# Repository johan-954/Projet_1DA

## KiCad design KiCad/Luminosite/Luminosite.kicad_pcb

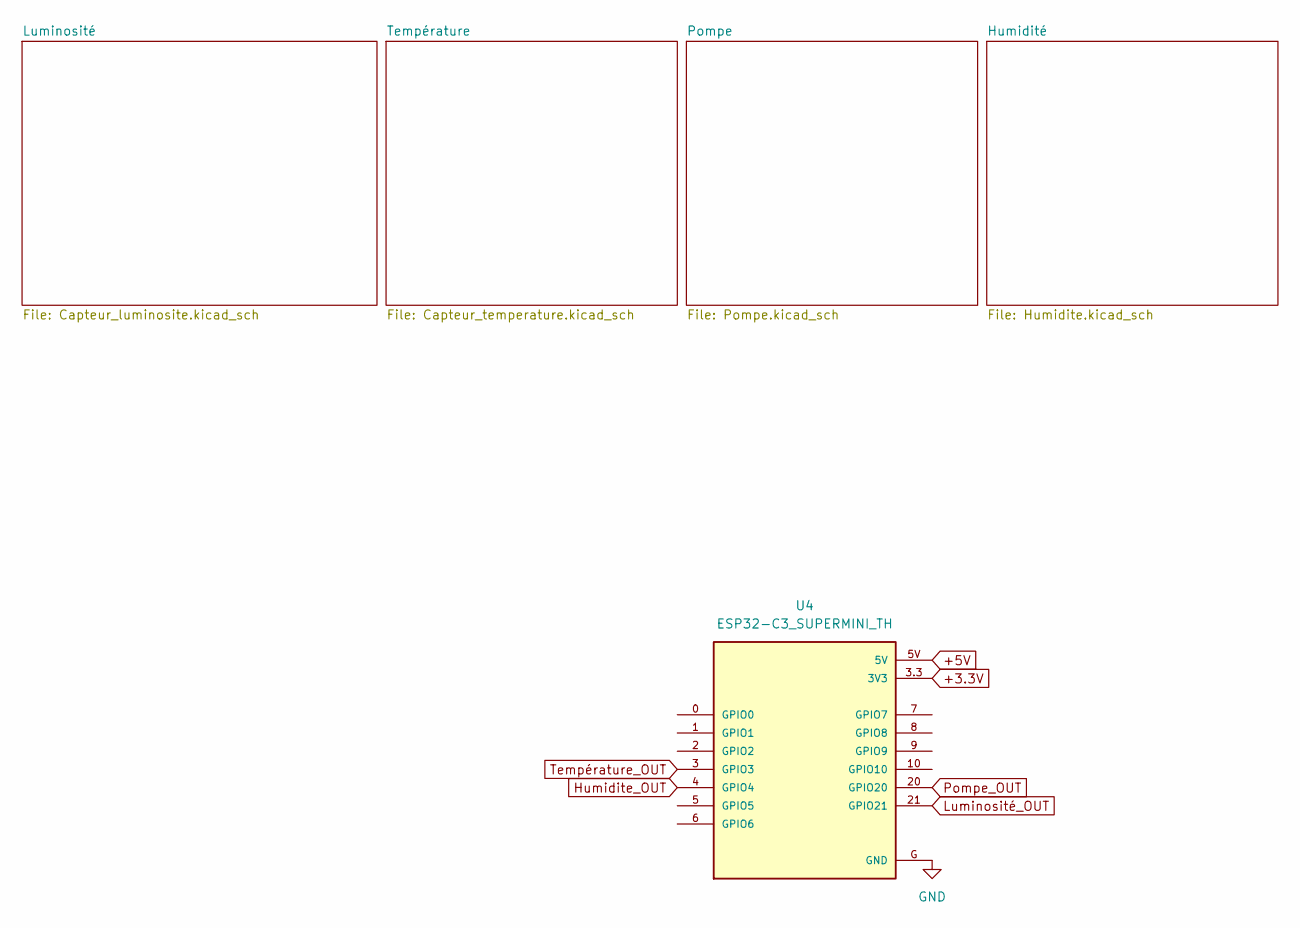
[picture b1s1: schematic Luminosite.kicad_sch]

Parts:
U4: ESP32-C3_SUPERMINI_TH; MODULE_ESP32-C3_SUPERMINI_TH

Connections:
+3.3V: U4.3.3 (3V3); also elsewhere on the board
+5V: U4.5V; also elsewhere on the board
GND: U4.G (GND); also elsewhere on the board
Humidite_OUT: U4.4 (GPIO4); also elsewhere on the board
Luminosité_OUT: U4.21 (GPIO21); also elsewhere on the board
Pompe_OUT: U4.20 (GPIO20); also elsewhere on the board
Température_OUT: U4.3 (GPIO3); also elsewhere on the board

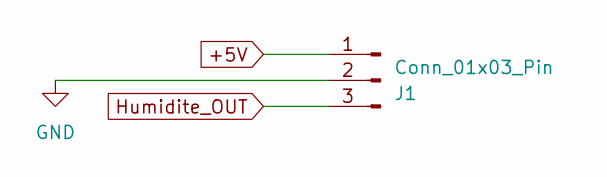
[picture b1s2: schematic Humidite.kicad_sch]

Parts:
J1: Conn_01x03_Pin; PinHeader_1x03_P2.54mm_Horizontal

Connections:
+5V: J1.1; also elsewhere on the board
GND: J1.2; also elsewhere on the board
Humidite_OUT: J1.3; also elsewhere on the board

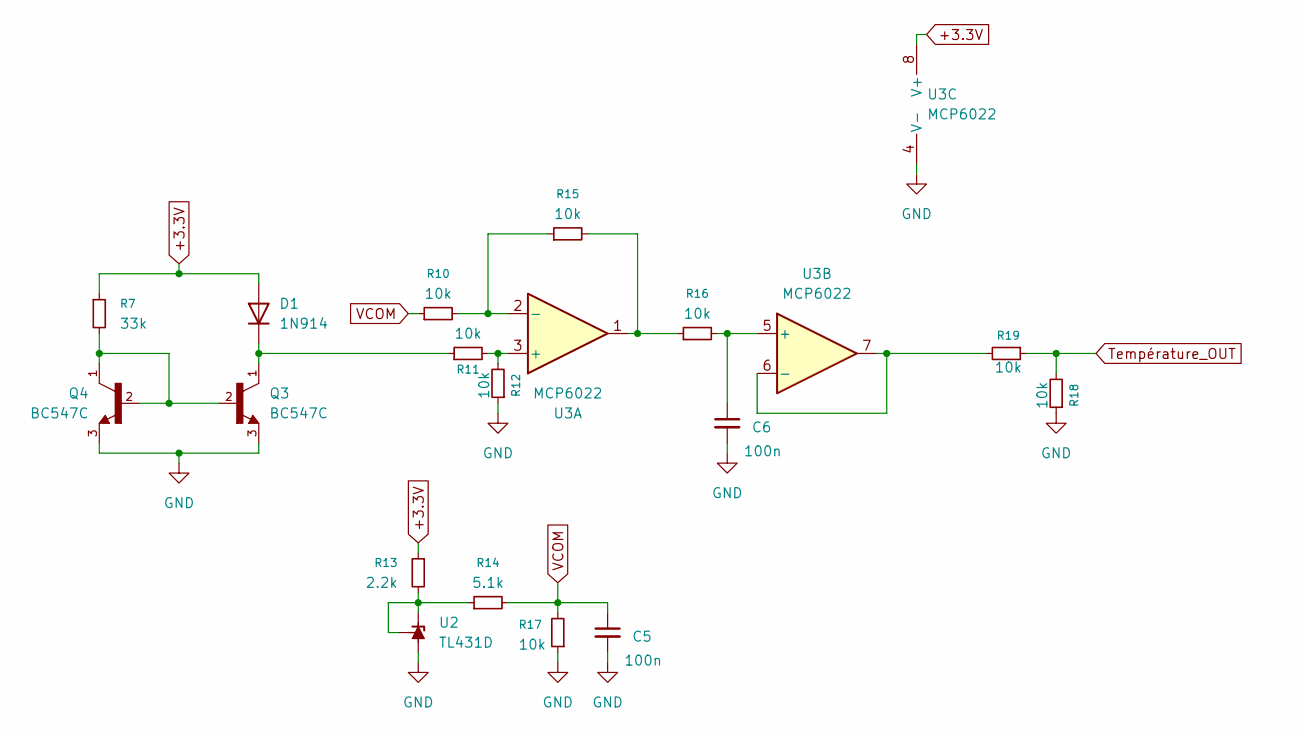
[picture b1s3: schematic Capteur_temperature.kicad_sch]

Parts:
C5, C6: 100n; C_0603_1608Metric_Pad1.08x0.95mm_HandSolder
D1: 1N914; D_DO-35_SOD27_P7.62mm_Horizontal
Q3, Q4: BC547C; TRANS_BC547C; PARTREV 2022-11-28
R7: 33k; R_0603_1608Metric_Pad0.98x0.95mm_HandSolder
R10, R11, R12, R15, R16, R17, R18, R19: 10k; R_0603_1608Metric_Pad0.98x0.95mm_HandSolder
R13: 2.2k; R_0603_1608Metric_Pad0.98x0.95mm_HandSolder
R14: 5.1k; R_0603_1608Metric_Pad0.98x0.95mm_HandSolder
U2: TL431D; SOIC-8_3.9x4.9mm_P1.27mm
U3: MCP6022; SOP8P65_300X640X120L60X24N

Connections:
+3.3V: D1.2 (A), R7.1, R13.1, U3.8 (V+); also elsewhere on the board
GND: C5.2, C6.2, Q3.3, Q4.3, R12.1, R17.1, R18.1, U2.2 (A), U2.3 (A), U2.6 (A), U2.7 (A), U3.4 (V-); also elsewhere on the board
unnamed: D1.1 (K), Q3.1, R11.1
unnamed: Q3.2, Q4.1, Q4.2, R7.2
unnamed: R15.2, R16.1, U3.1
unnamed: R13.2, R14.1, U2.1 (K), U2.8 (REF)
unnamed: R11.2, R12.2, U3.3 (+)
unnamed: R10.2, R15.1, U3.2 (-)
unnamed: C6.1, R16.2, U3.5 (+)
unnamed: R19.2, U3.6 (-), U3.7
Température_OUT: R18.2, R19.1; also elsewhere on the board
VCOM: C5.1, R10.1, R14.2, R17.2

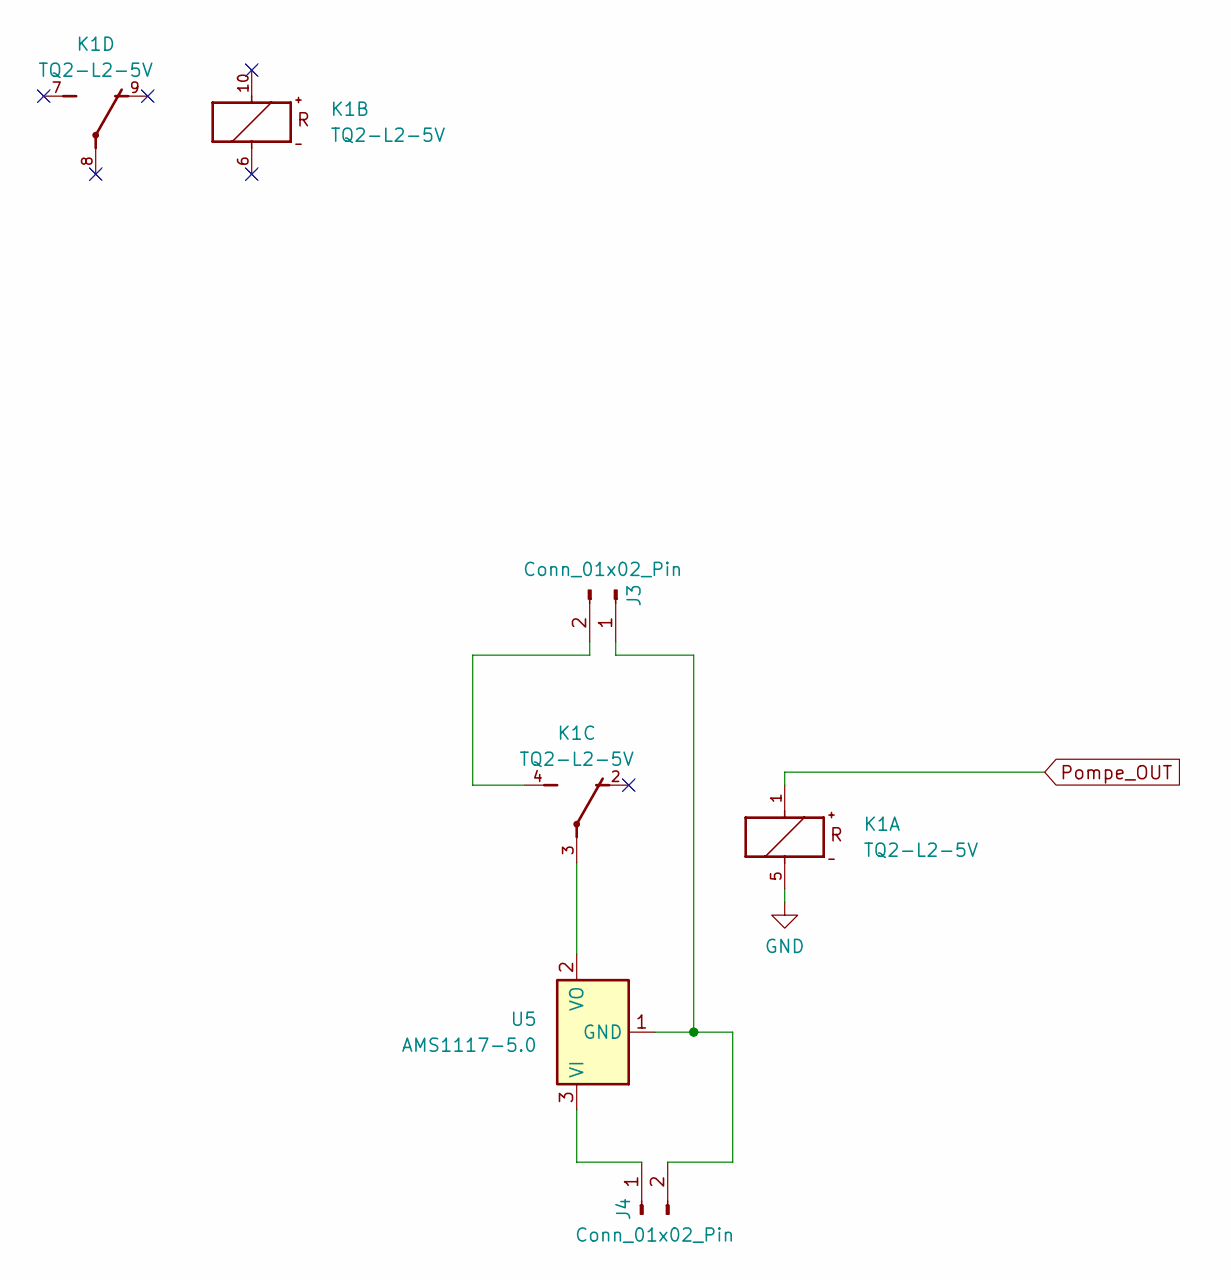
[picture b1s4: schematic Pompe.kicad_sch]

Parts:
J3, J4: Conn_01x02_Pin; PinHeader_1x02_P2.54mm_Horizontal
K1: TQ2-L2-5V; TQ2; FARNELL 1175718
U5: AMS1117-5.0; SOT-223-3_TabPin2

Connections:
GND: K1.5; also elsewhere on the board
unnamed: J3.1, J4.2, U5.1 (GND)
unnamed: J3.2, K1.4
unnamed: J4.1, U5.3 (VI)
unnamed: K1.3, U5.2 (VO)
Pompe_OUT: K1.1; also elsewhere on the board

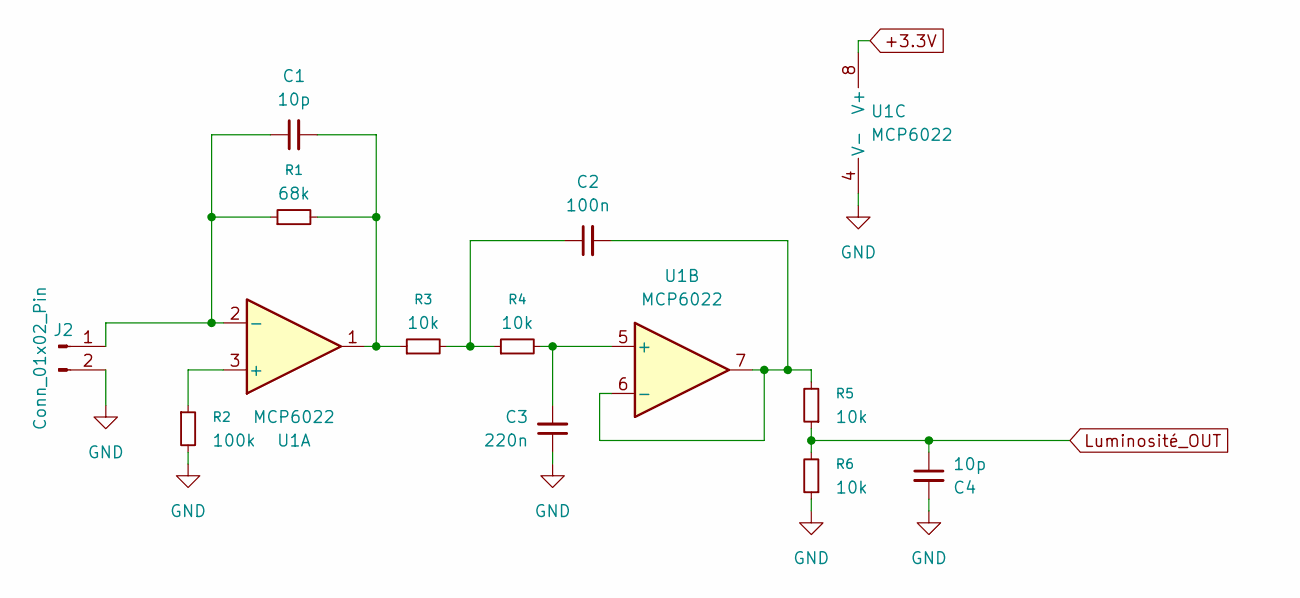
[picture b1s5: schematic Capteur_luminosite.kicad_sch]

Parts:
C1, C4: 10p; C_0603_1608Metric_Pad1.08x0.95mm_HandSolder
C2: 100n; C_0603_1608Metric_Pad1.08x0.95mm_HandSolder
C3: 220n; C_0603_1608Metric_Pad1.08x0.95mm_HandSolder
J2: Conn_01x02_Pin; PinHeader_1x02_P2.54mm_Horizontal
R1: 68k; R_0603_1608Metric_Pad0.98x0.95mm_HandSolder
R2: 100k; R_0603_1608Metric_Pad0.98x0.95mm_HandSolder
R3, R4, R5, R6: 10k; R_0603_1608Metric_Pad0.98x0.95mm_HandSolder
U1: MCP6022; SOP8P65_300X640X120L60X24N

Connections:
+3.3V: U1.8 (V+); also elsewhere on the board
GND: C3.1, C4.2, J2.2, R2.2, R6.1, U1.4 (V-); also elsewhere on the board
Luminosité_OUT: C4.1, R5.1, R6.2; also elsewhere on the board
unnamed: C1.2, R1.2, R3.1, U1.1
unnamed: C2.1, R3.2, R4.1
unnamed: C1.1, J2.1, R1.1, U1.2 (-)
unnamed: R2.1, U1.3 (+)
unnamed: C3.2, R4.2, U1.5 (+)
unnamed: C2.2, R5.2, U1.6 (-), U1.7

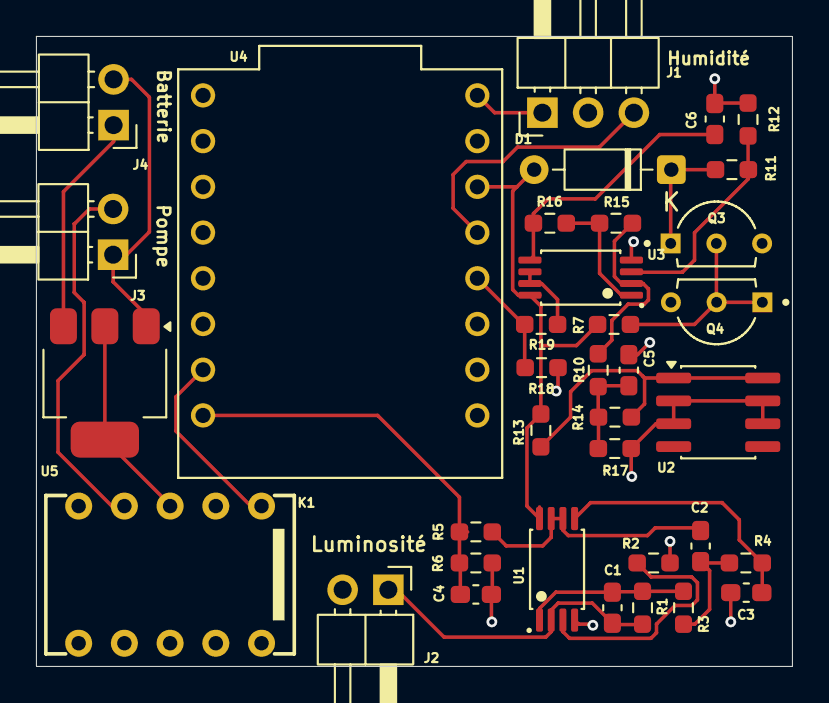
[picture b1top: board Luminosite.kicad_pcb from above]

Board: 2 copper layers, 42.0 x 35.0 mm, 36 parts (0 on the bottom side), 26 nets.

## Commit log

2026-04-19 Création du projet et ajout des anciens fichiers
2026-04-19 Schéma Kicad luminosité
2026-04-19 Ajout des fichiers LTspice
2026-04-19 Nommage des fichiers LTspice
2026-04-20 Ajout Dossiers technique
2026-04-20 Capteur de température
2026-04-20 Schéma LTspice temperature
2026-05-04 Ajout des empreintes pour le PCB
2026-05-04 Ajout du Schéma Pompe
2026-05-04 Commencement du PCB
2026-05-05 Modification du PCB
2026-05-05 PCB Terminé
2026-05-06 Doc Commande
2026-05-06 Finalisation PCB
